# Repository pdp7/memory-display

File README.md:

## OSH Park shared project
* [SHARP memory display and Teensy LC](https://oshpark.com/projects/4Hbq9Awy)

## Bill of Materials
* [SHARP Memory Display Breakout - 1.3" 96x96 Silver Monochrome](https://www.adafruit.com/product/1393)
* [Teensy LC - OSH Park Edition](http://store.oshpark.com/products/teensy-lc)
* [Adafruit BME280 sensor *(Temp/Hum/Press)*](https://www.adafruit.com/product/2652)

## Video
* [Short demo](https://www.youtube.com/watch?v=esPlImZcRdI)
* [Full demo](https://www.youtube.com/watch?v=OchR3nb700U)

## Photos
* [Google+ gallery](https://plus.google.com/photos/+DrewFustini/albums/6319926590582577217)
* [images gallery](https://github.com/pdp7/memory-display/tree/master/images)
* 

## License
This project released under the CERN Open Hardware v1.2 License

**Note:** `memory-display.ino` based on library code and example code from [Adafruit Industries](http://adafruit.com/)

## Contact
* Drew Fustini &lt;drew@oshpark.com&gt;

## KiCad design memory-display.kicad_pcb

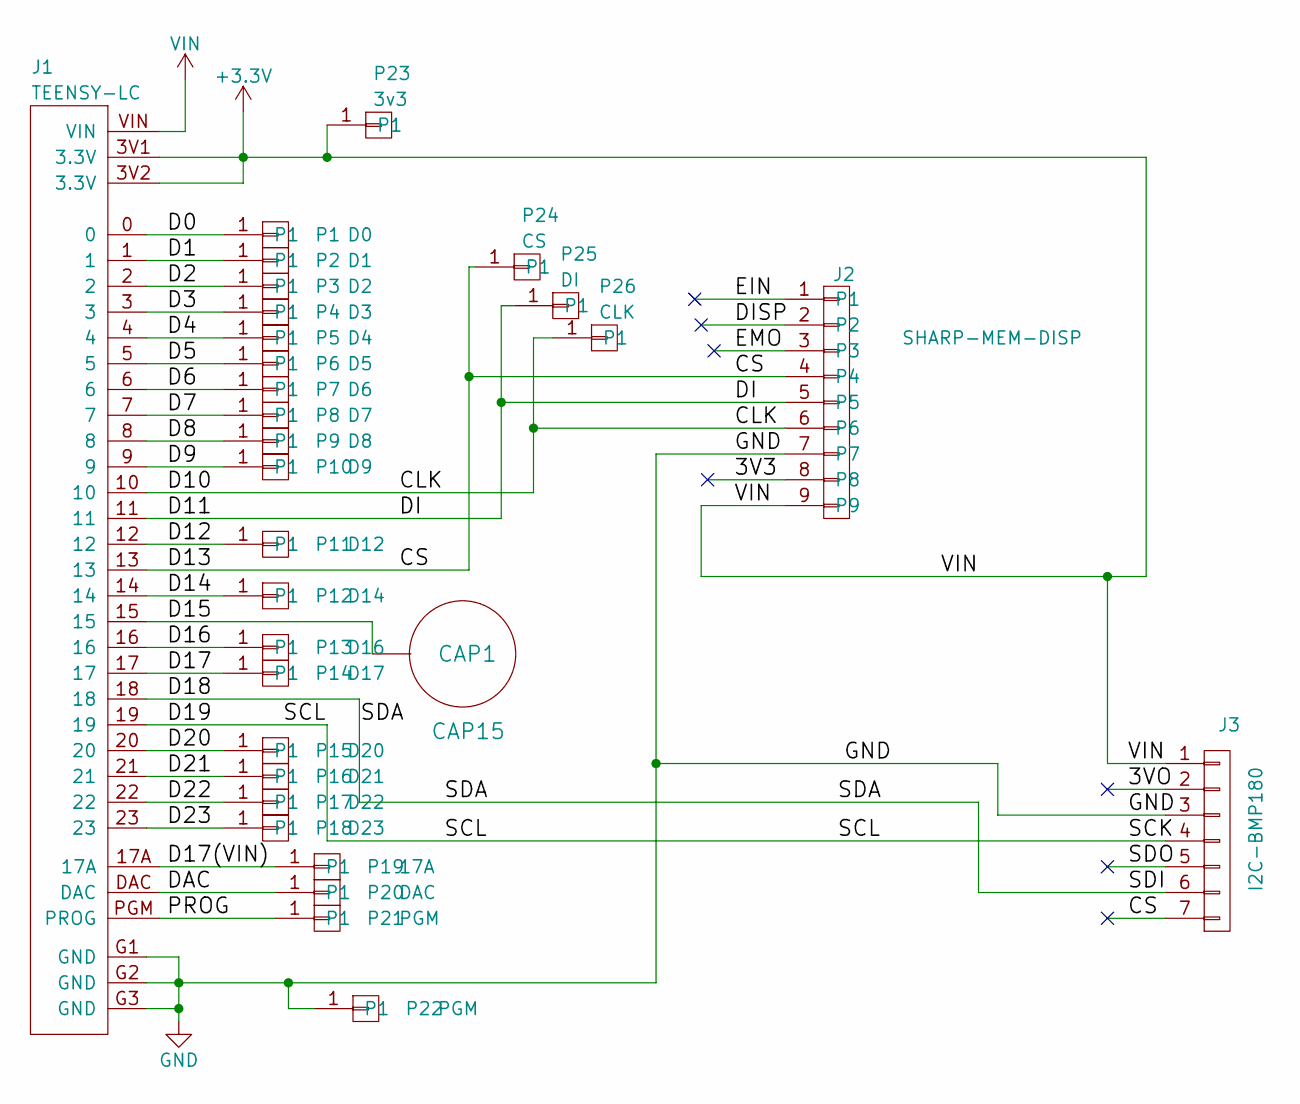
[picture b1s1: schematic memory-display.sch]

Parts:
CAP1: CAP15; CAPSENSE-CIRCLE-D10MM
J1: TEENSY-LC
J2: SHARP-MEM-DISP; CONN-HEADER-STRAIGHT-P2.54MM-1x09
J3: I2C-BMP180; CONN-HEADER-STRAIGHT-P2.54MM-1x07
P1: D0; CONN-HEADER-STRAIGHT-P2.54MM-1x01
P2: D1; CONN-HEADER-STRAIGHT-P2.54MM-1x01
P3: D2; CONN-HEADER-STRAIGHT-P2.54MM-1x01
P4: D3; CONN-HEADER-STRAIGHT-P2.54MM-1x01
P5: D4; CONN-HEADER-STRAIGHT-P2.54MM-1x01
P6: D5; CONN-HEADER-STRAIGHT-P2.54MM-1x01
P7: D6; CONN-HEADER-STRAIGHT-P2.54MM-1x01
P8: D7; CONN-HEADER-STRAIGHT-P2.54MM-1x01
P9: D8; CONN-HEADER-STRAIGHT-P2.54MM-1x01
P10: D9; CONN-HEADER-STRAIGHT-P2.54MM-1x01
P11: D12; CONN-HEADER-STRAIGHT-P2.54MM-1x01
P12: D14; CONN-HEADER-STRAIGHT-P2.54MM-1x01
P13: D16; CONN-HEADER-STRAIGHT-P2.54MM-1x01
P14: D17; CONN-HEADER-STRAIGHT-P2.54MM-1x01
P15: D20; CONN-HEADER-STRAIGHT-P2.54MM-1x01
P16: D21; CONN-HEADER-STRAIGHT-P2.54MM-1x01
P17: D22; CONN-HEADER-STRAIGHT-P2.54MM-1x01
P18: D23; CONN-HEADER-STRAIGHT-P2.54MM-1x01
P19: 17A; CONN-HEADER-STRAIGHT-P2.54MM-1x01
P20: DAC; CONN-HEADER-STRAIGHT-P2.54MM-1x01
P21, P22: PGM; CONN-HEADER-STRAIGHT-P2.54MM-1x01
P23: 3v3; CONN-HEADER-STRAIGHT-P2.54MM-1x01
P24: CS; CONN-HEADER-STRAIGHT-P2.54MM-1x01
P25: DI; CONN-HEADER-STRAIGHT-P2.54MM-1x01
P26: CLK; CONN-HEADER-STRAIGHT-P2.54MM-1x01

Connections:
+3V3: J1.3V1 (3.3V), J1.3V2 (3.3V), J1.VIN, J2.9, J3.1, P23.1
/3V3: J2.8
/3VO: J3.2
/CLK: J1.10, J2.6, P26.1
/CS: J1.13, J2.4, J3.7, P24.1
/D0: J1.0, P1.1
/D1: J1.1, P2.1
/D2: J1.2, P3.1
/D3: J1.3, P4.1
/D4: J1.4, P5.1
/D5: J1.5, P6.1
/D6: J1.6, P7.1
/D7: J1.7, P8.1
/D8: J1.8, P9.1
/D9: J1.9, P10.1
/D11: J1.11, J2.5, P25.1
/D12: J1.12, P11.1
/D14: J1.14, P12.1
/D15: CAP1.1, J1.15
/D16: J1.16, P13.1
/D17: J1.17, P14.1
/D17(VIN): J1.17A, P19.1
/D18: J1.18, J3.6
/D19: J1.19, J3.4
/D20: J1.20, P15.1
/D21: J1.21, P16.1
/D22: J1.22, P17.1
/D23: J1.23, P18.1
/DAC: J1.DAC, P20.1
/DISP: J2.2
/EIN: J2.1
/EMO: J2.3
/PROG: J1.PGM (PROG), P21.1
/SDO: J3.5
GND: J1.G1 (GND), J1.G2 (GND), J1.G3 (GND), J2.7, J3.3, P22.1

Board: 2 copper layers, 30 parts (0 on the bottom side), 29 nets, no tracks yet.

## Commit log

2016-07-24 test
2016-07-24 add BoM
2016-07-25 finished schematic and start layout
2016-07-26 finish layout
2016-08-16 refactor directory structure and add Arduino code
2016-08-17 read cap touch button
2016-08-23 add images
2016-08-23 invert display every 1 second
2016-08-26 toggle display mode when button pressed
2016-09-09 switch from BME280 sensor to BMP280
    I do not have an Adafruit BME280 sensor breakout board
    to use for this project at the moment. I've switched
    to the BMP280 which has the same pinout but does not
    have humidity sensor. I've changed the display code
    to display just temperature, altitude and pressure.
2016-09-09 Revert "switch from BME280 sensor to BMP280"
    This reverts commit cdd505683a4165569ee07a68f52abad231dc8b78.
    bmp280 branch should be used instead of master

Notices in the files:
memory-display.kicad_pcb:
Released under the CERN Open Hardware License v1.2
